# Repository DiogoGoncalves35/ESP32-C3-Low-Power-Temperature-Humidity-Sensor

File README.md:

# ESP32-C3-Low-Power-Temperature-Humidity-Sensor

This board is designed arround SHT31 sensor and ESP32-C3 microcontroller. It's a low power board, arround 6 µA during deep sleep, it's super efficient during communication, makes it perfect to be powered with a Li-Ion battery. The next image shows version 2.0.

Two versions were designed, the first was a experimental board and the second the final one. The second version solved the problems found on the first and also added a circuit to control the voltage divider, this helped reduce the deep sleep current by 9 µA.

|                           | V1.0          | V2.0          | 
| ------------              | ------------  | ------------  | 
| Current Deep Sleep (µA)   | 13.33         | 6.03          | 

The microcontroller wakes every 5 minutes to do the measurement and send the data. With this value, the device can last up to 1800 days with a 550 mAh Li-Ion battery. This is a estimated  value because it's not easy to calculate the exact one, the system doesn't consume the exact ammount every cycle and the battery datasheet doesn't state the BMS drawn current. 

------------

### Communication Protocol 

In order to choose the most efficient protocol, three tests were executed between BLE, ESP-NOW and MQTT. The first test was about message delivering, each test corresponds to sending messages every 5 minutes for 24 hours (288 messages per day). 

The values on the table show the average result for 10 tests.

|               | ESP-NOW       | MQTT          | BLE (NimBLE)  |
| ------------  | ------------  | ------------  | ------------  |
| Average (%)   | 100.0         | 97.4          | 99.8          |

ESP-NOW was the only protocol to delivery every message. 

MQTT couldn't get 100% in any test, it lost about 3 to 8 messages per test, this loss could be related to the library used not support QoS 0. In case the broker didn't receive the packet 750 ms after the first send, another one was published and if after 750 ms the broker still didn't received, the board entered deep sleep. Wi-Fi connection with fixed IP.

BLE in 6 tests delivered every message and in the others lost about 2 to 4 messages, for the test NimBLE library was used, the default BLE library has many problems related to memory.

The last test is about the average current and time during execution. The values on the table show the average result for 10 measurements. The time corresponds to the moment the ESP wakes from deep sleep and goes into deep sleep.

|               | ESP-NOW       | MQTT          | BLE (NimBLE)  |
| ------------  | ------------  | ------------  | ------------  |
| Current (mA)  | 28.76         | 69.65         | 80.57         |
| Time (ms)     | 85.31         | 906.26        | 737.57        |

ESP-NOW is by far the most efficient protocol, the way it's built allows communication to be direct and fast. Since it only uses the antenna to send the message, it's possible to achive low current during execution.

MQTT needs about 300-400 ms to connect to Wi-Fi and MQTT server, without fixed IP, connection time increases in 2 to 3 seconds. Average current increases compared to ESP-NOW because the antenna is used several times.

BLE uses the antenna quite often because needs to adverstise the device, services and then transmit data to the other device. Eventhought it uses lower current, the average current is higher compared to MQTT.

|                   | ESP-NOW       | MQTT          | BLE (NimBLE)  |
| ------------      | ------------  | ------------  | ------------  |
| Difference (%)    | ---           | 96.10         | 95.90         |

ESP-NOW is 96.10% more efficient then MQTT and 95.90% then BLE.

After the results of both tests, ESP-NOW protocol was chose.

---

### Code 

The microcontroller saves the last reading in the RTC memory, by doing this it's possible to compare the values just measured to the ones stored in the memory. This allows the system to not send the message in case the measurements are the same and increases battery life.

```arduino
//Variables to store last measurement
RTC_DATA_ATTR double    RTC_Temperature = 0;
RTC_DATA_ATTR byte      RTC_Humidity    = 0;

// Block code after measurement
if(Data.Temperature == RTC_Temperature && Data.Humidity == RTC_Humidity)
{
    // Start deep sleep
    esp_deep_sleep_start();
}
else
{
    // Store values 
    RTC_Temperature = Data.Temperature;
    RTC_Humidity    = Data.Humidity;
}
```

The board responsible for receiving data needs to have the same data structure.

```arduino
// ESP-NOW data structure   
typedef struct struct_message 
{
  byte   ID = X;               // Board identifier
  float  Temperature;          // Temperature variable
  byte   Humidity;             // Humidity variable
  byte   Battery_Percentage;   // Battery percentage variable
} struct_message;

struct_message Data;
```

The frequency that the code runs impacts current and time of execution. The code was divide in two phases, the first is from the moment the board wakes from deep sleep to the moment it starts the ESP-NOW function, the second is from the start of ESP-NOW function to the moment it enters in deep sleep. After some measurements done, the results showed 40-160 MHz was the most efficient combination. In case the microcontroller sends every message, running with fixed 160 MHz is more efficient.

---

### Schematic 

The [schematic](/Hardware/PCB/Schematic.pdf) is arround ESP32-C3 microcontroller and SHT31 sensor. The P-Channel Mosfet BSS84 and the N-Channel Transistor S8050 control the voltage for the voltage divider. The board is designed to be powered with a Li-Ion battery that includes a BMS.

------------

### PCB

[This](Hardware/PCB/) 1.6mm board contains 4 layers with the stackup Signal+Power/GND/GND/Signal+Power. GND area was removed closer to the sensor in order to not affect readings. The pogo pin connector is for programming the microcontroller. The reset button is located on the back.

---

### Known issues

- None

------------

### To-Do

- TPL5110 Timer to control the microcontroller and reduce deep sleep current

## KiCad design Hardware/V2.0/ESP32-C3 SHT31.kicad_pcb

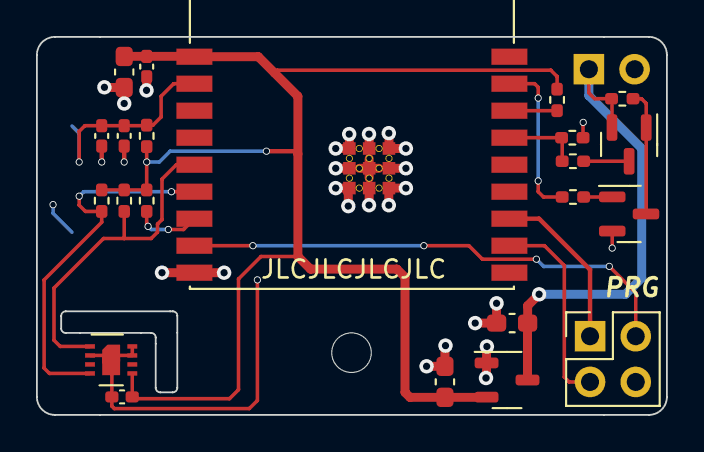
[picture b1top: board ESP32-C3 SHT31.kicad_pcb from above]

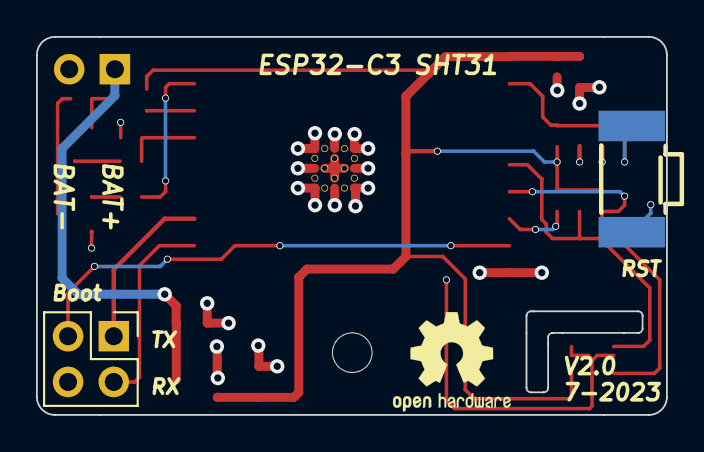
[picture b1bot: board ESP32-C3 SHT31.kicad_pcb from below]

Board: 4 copper layers, 35.0 x 21.0 mm, 24 parts (2 on the bottom side), 16 nets.

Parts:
BT1: Li-Ion- 550 mAh; PinHeader_1x02_P2.54mm_Horizontal
C2, C3, C7: 0.1 uF; C_0402_1005Metric_Pad0.74x0.62mm_HandSolder
C4, C8, C9: 10 uF; C_0603_1608Metric_Pad1.08x0.95mm_HandSolder
C5: 10 uF; C_0402_1005Metric_Pad0.74x0.62mm_HandSolder
J2: Pogo Pins; PinHeader_2x02_P2.54mm_Vertical
Q1: BSS84; SOT-23
Q2: S8050; SOT-23
R1, R6, R7, R8, R9: 10k; R_0402_1005Metric_Pad0.72x0.64mm_HandSolder
R2, R3: 220k; R_0402_1005Metric_Pad0.72x0.64mm_HandSolder
R4, R5: 2k2; R_0402_1005Metric_Pad0.72x0.64mm_HandSolder
SW1: RST; KEY-SMD_KSS-2G
U1: ESP32-C3-WROOM-02-N4; MODULE_ESP32-C3-WROOM-02-H4
U2: SHT31-DIS-B2.5kS; Sensirion_DFN-8-1EP_2.5x2.5mm_P0.5mm_EP1.1x1.7mm
U3: MD5233; SOT-23-3

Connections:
+3.3V: C3.2, C4.1, C7.2, C9.1, R1.1, R4.1, R5.1, R6.1, R7.1, U1.1 (3V3), U2.5 (VDD), U3.2 (VO)
+BATT: BT1.1 (+), C8.1, Q1.2 (S), R8.1, U3.3 (VI)
/ADC: R2.2, R3.2, U1.15 (IO3)
/ADC_EN: R9.1, U1.17 (IO1)
/BOOT: J2.2, U1.8 (IO9)
/ESP32_EN: C2.1, C5.2, R1.2, SW1.1, U1.2 (EN)
/ESP32_RX: J2.3, U1.11 (RXD)
/ESP32_TX: J2.1, U1.12 (TXD)
/I2C_SCL: R5.2, U1.6 (IO7), U2.4 (SCL)
/I2C_SDA: R4.2, U1.5 (IO6), U2.1 (SDA)
/IO2: R6.2, U1.16 (IO2)
/IO8: R7.2, U1.7 (IO8)
GND: BT1.2 (-), C2.2, C3.1, C4.2, C5.1, C7.1, C8.2, C9.2, J2.4, Q2.2 (E), R3.1, SW1.2, U1.9 (GND), U1.19 (GND), U1.20 (GND), U1.21 (GND), U1.22 (GND), U1.23 (GND), U1.24 (GND), U1.25 (GND), U1.26 (GND), U1.27 (GND), U1.28 (GND), U1.29 (GND), U1.30 (GND), U1.31 (GND), U1.32 (GND), U1.33 (GND), U1.34 (GND), U1.35 (GND), U1.36 (GND), U1.37 (GND), U1.38 (GND), U1.39 (GND), U2.2 (ADDR), U2.7 (R), U2.8 (VSS), U2.9 (VSS), U3.1 (GND)
unnamed: Q1.3 (D), R2.1
unnamed: Q1.1 (G), Q2.3 (C), R8.2
unnamed: Q2.1 (B), R9.2

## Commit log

2024-01-21 Publish
